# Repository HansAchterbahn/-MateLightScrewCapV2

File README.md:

# MateLight-ScrewCap-V2

## Idea

My MateLight project is based on the idea of [jaseg's MateLight](https://github.com/jaseg/matelight) and improves it with a APA102 LED screw cap PCB which is easy to install and easy to remove from the coasters. An overview about my MateLight project you can find on my [MateLight overview page](https://github.com/HansAchterbahn/MateLightScrewCap-PowerSupply).

## This Repo

In this Repository you can find version 0.2.x of the MateLight-ScrewCap PCB which is made to screw it to a Mate bottle.

You can find following details:
- PCB schematics and board layouts (created in Kicad),
- PCB Gerber data (ready for manufacturing),
- a bill of material (with device ordering numbers) and
- a 3D model of the PCB.

*Fork me and have fun!*

## Power source

An APA102C LED consumes a maximum of 60 mA (red/green/blue each 20 mA). Because of that scince v0.2.0 every screw cap has its own power supply. To connect the power supply of every screw cap in a crate you need the power distributor in this repo.

```
                  LED1                                                   LED19                                   LED20
                 (APA102)                                               (APA102)                                (APA102)
                ----------                                             ----------                              ----------
     .--. Clock |   __   | Clock .--.                       .--. Clock |   __   | Clock .--.        .--. Clock |   __   | Clock .--.
     |  |--->---|  /  \  |---> --|  |                       |  |--->---|  /  \  |--->---|  |        |  |--->---|  /  \  |--->---|  |
     |  | Data  | (    ) | Data  |  |          ooo          |  | Data  | (    ) | Data  |  |        |  | Data  | (    ) | Data  |  |
     |  |--->---|  \__/  |--->---|  |                       |  |--->---|  \__/  |--->---|  |        |  |--->---|  \__/  |--->---|  |
     '--'       |        |       '--'                       '--'       |        |       '--'        '--'       |        |       '--'
                ----------                                             ----------                              ---------|
    Input          |  |         Output                     Input          |  |         Output      Input          |  |         Output
  Connector     5V |  | GND    Connector                 Connector     5V |  | GND    Connector  Connector     5V |  | GND    Connector
                  .----.                                                 .----.                                  .----.
                  |    |                                                 |    |                                  |    |
                  '----'                                                 '----'                                  '----'
                  Power                                                  Power                                   Power
                 Connector                                              Connector                               Connector
```

## PCB 3D view

Animated 3D STL model: [kibot/3d/model](kibot/3d/model)

__Top view__

__Bottom view__

## Schematic

## Board

__Top view__

__Bottom view__

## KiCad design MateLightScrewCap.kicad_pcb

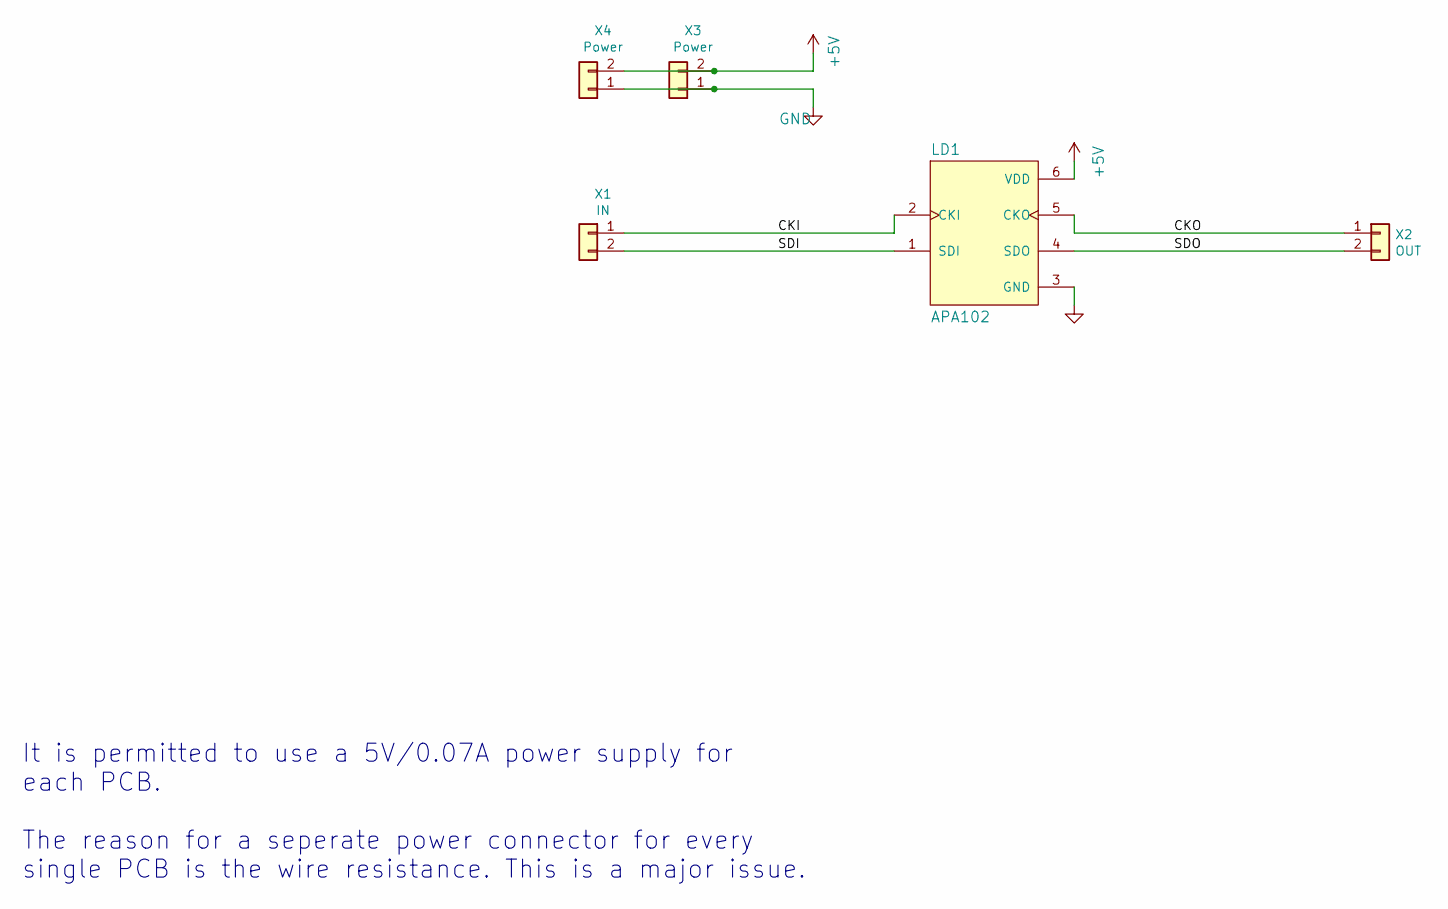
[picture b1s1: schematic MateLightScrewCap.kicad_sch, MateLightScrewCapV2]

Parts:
LD1: APA102; APA102C-5050
X1: IN; JST_S2B-ZR-SM4A-TF(LF)(SN)
X2: OUT; JST_S2B-ZR-SM4A-TF(LF)(SN)
X3: Power; JST_S2B-PH-SM4-TB(LF)(SN)
X4: Power; JST_S2B-ZR-SM4A-TF(LF)(SN)

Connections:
+5V: LD1.6 (VDD), X3.2, X4.2
/CKI: LD1.2 (CKI), X1.1
/CKO: LD1.5 (CKO), X2.1
/SDI: LD1.1 (SDI), X1.2
/SDO: LD1.4 (SDO), X2.2
GND: LD1.3 (GND), X3.1, X4.1

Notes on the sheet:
It is permitted to use a 5V/0.07A power supply for each PCB. The reason for a seperate power connector for every single PCB is the wire resistance. This is a major issue.

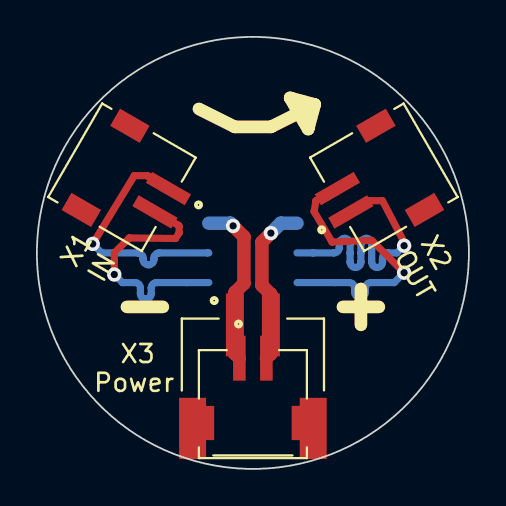
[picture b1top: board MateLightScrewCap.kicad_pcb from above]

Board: 2 copper layers, 24.0 x 24.0 mm, 5 parts (1 on the bottom side), 6 nets.

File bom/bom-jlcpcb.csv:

Comment,Designator,Footprint,LCSC Part #
APA102 ,LD1,APA102C-5050,
"S4B-PH-SM4 Generic connector, single row, 01x04, script generated (kicad-library-utils/schlib/autogen/connector/)","X1,X2",JST_S4B-PH-SM4-TB,

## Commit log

2022-09-04 First version of v0.2.0 created - separate connector for power supply to solve problems with current supply in a mate crate
2022-09-10 Created DXF Export
2022-09-10 Created Gerber export
2022-09-10 Added 3D models to project data
2022-09-10 Port project to KiCad v6 + Small changes
2022-09-10 Optimized data tracks to exact same length
2022-09-10 Solved ERC issues
2022-09-11 Update DXF output
2022-09-11 Update Gerber output
2022-09-11 Update project settings
2022-09-12 Small improvements
2022-09-12 Update interactive BOM (ibom)
2022-09-12 Update Kibot yaml file: Export locations
2022-10-08 Clean Repo
2022-10-08 Add kibot export
2022-10-08 Add readme and license

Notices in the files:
MateLightScrewCap.kicad_pcb:
MIT License
MateLightScrewCap.kicad_sch:
Licence: MIT Licence
